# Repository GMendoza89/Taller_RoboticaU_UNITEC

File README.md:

# Taller_Robotica_UNITEC
Repositorio del taller de Robótica de la UNITEC Campus Queretaro. En el podras encontrar los ejemplos que que se van realizando durante el curso. 

## C++

Aqui encontraras los ejemplos que se realizaron en las clases de repaso de C++, y el paradigma orientado a objetos.

## Arduino

En esta seccion encontraras ejemplos de como construir tu propia libreria para generar las clases de tus componentes. Tambien encontraras los sketch, donde
se como declarar, y utilizar los sensores, actuadores y los diferentes módulos que puedan ser utilizados en Arduino.

### Hola_Mundo
Diferentes ejemplos de como crear el primer sketch de Arduino, el cual es prender y apagar un LED. 

### Analog_IO
Ejemplos de como declarar entradas y salidas analogicas.

### Digital_IO
Ejemplo de como utilizar entradas y salidas digitales.

### Libreria componentes
Libreria creada para el curso en que se tienen clases de componentes que se utilizan en los diferentes ejemplos. 
	- Clase LED. abtracción de un LED para su uso en IDE de Arduino.
	- Clase LED_RGB. Abstracción de LED RGB para su uso en IDE de Arduino.
	- Clase Buttom. Abstracción de un Switch o push buttom para su uso en IDE de Arduino.
	- Clase Pot. Abstracción de un potenciometro, para su uso en IDE de Arduino.
	- Clase shiftR74HC595. Abtracción para de circuito de desplazamiento para su uso en IDE de Arduino.
	- Clase ultrasonico. Abstracción de sensor ultrasonico HC-SR04. para su uso en IDE de Arduino.
	- Clase DC_Motor. Abtracción de un motor o motoreductor en CD, para su uso con un puente H y la IDE de Arduino.

## Robot Shield
Placa de circuito Impreso diseñada, como interface entre los sensores y actuadores de un robot diferencial, y una targeta de desarrollo Arduino UNO y compactibles.
Cuenta con las interfaces para los siguinetes puertos:
	- Coneccion con punte H L293D para control de dos motores en DC.
	- Un servomotor
	- Un Sensor Ultrasónico HC - SR04
	- Tira de sensores reflectivos compactibles con siguelineas
	- Modulo Bluetooth HC-06

## Python

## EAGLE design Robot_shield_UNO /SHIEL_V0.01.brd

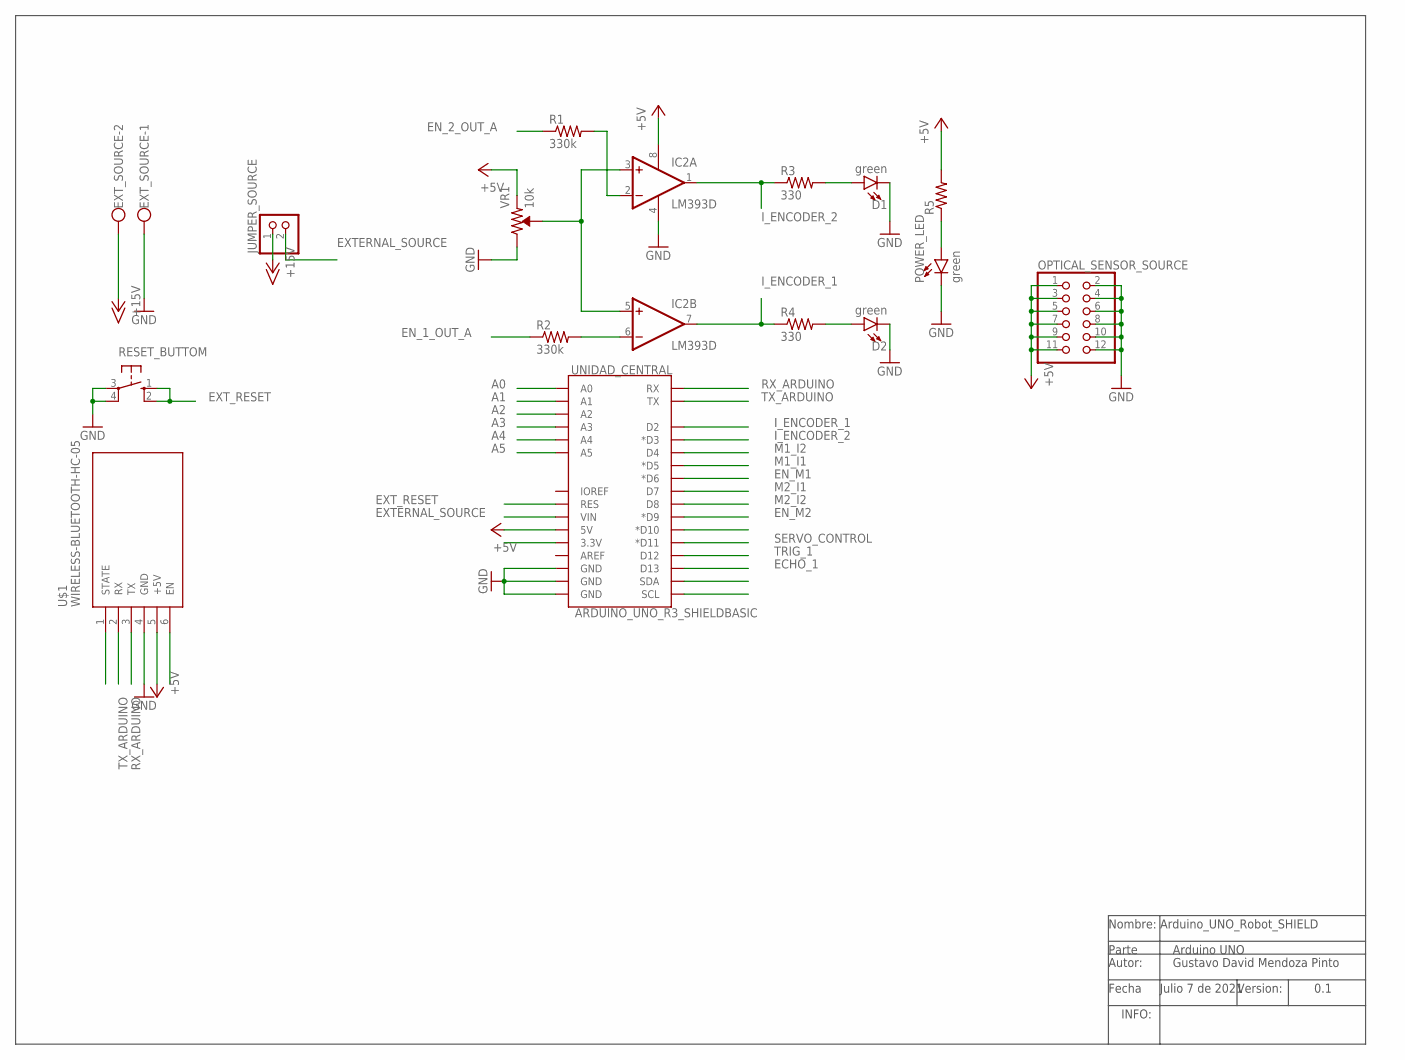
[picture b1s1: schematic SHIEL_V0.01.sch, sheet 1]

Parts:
D1, D2: green; LED_3MM-NS
EXT_SOURCE: W237-102
IC2: LM393D; SO08
JUMPER_SOURCE: PINHD-1X2; 1X02
OPTICAL_SENSOR_SOURCE: PINHD-2X6; 2X06
POWER_LED: green; LED_3MM-NS
R1, R2: 330k; M2012
R3, R4: 330; M2012
R5: R-US_M2012; M2012
RESET_BUTTOM: 10-XX; B3F-10XX
U$1: WIRELESS-BLUETOOTH-HC-05
UNIDAD_CENTRAL: ARDUINO_UNO_R3_SHIELDBASIC; UNO_R3_SHIELD
VR1: 10k; TRIMPOT-PTH-3386U

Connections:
+5V: IC2.8 (V+), OPTICAL_SENSOR_SOURCE.1, OPTICAL_SENSOR_SOURCE.3, OPTICAL_SENSOR_SOURCE.5, OPTICAL_SENSOR_SOURCE.7, OPTICAL_SENSOR_SOURCE.9, OPTICAL_SENSOR_SOURCE.11, R5.2, U$1.5 (+5V), UNIDAD_CENTRAL.5V, VR1.1 (CCW); also elsewhere on the board
+15V: EXT_SOURCE.2, JUMPER_SOURCE.1
A0: UNIDAD_CENTRAL.A0; also elsewhere on the board
A1: UNIDAD_CENTRAL.A1; also elsewhere on the board
A2: UNIDAD_CENTRAL.A2; also elsewhere on the board
A3: UNIDAD_CENTRAL.A3; also elsewhere on the board
A4: UNIDAD_CENTRAL.A4; also elsewhere on the board
A5: UNIDAD_CENTRAL.A5; also elsewhere on the board
ECHO_1: UNIDAD_CENTRAL.D13; also elsewhere on the board
EN_1_OUT_A: R2.1; also elsewhere on the board
EN_2_OUT_A: R1.1; also elsewhere on the board
EN_M1: UNIDAD_CENTRAL.D6 (*D6); also elsewhere on the board
EN_M2: UNIDAD_CENTRAL.D9 (*D9); also elsewhere on the board
EXTERNAL_SOURCE: JUMPER_SOURCE.2, UNIDAD_CENTRAL.VIN; also elsewhere on the board
EXT_RESET: RESET_BUTTOM.1 (S), RESET_BUTTOM.2 (S1), UNIDAD_CENTRAL.RES
GND: D1.K (C), D2.K (C), EXT_SOURCE.1, IC2.4 (V-), OPTICAL_SENSOR_SOURCE.2, OPTICAL_SENSOR_SOURCE.4, OPTICAL_SENSOR_SOURCE.6, OPTICAL_SENSOR_SOURCE.8, OPTICAL_SENSOR_SOURCE.10, OPTICAL_SENSOR_SOURCE.12, POWER_LED.K (C), RESET_BUTTOM.3, RESET_BUTTOM.4 (P1), U$1.4 (GND), UNIDAD_CENTRAL.GND@0 (GND), UNIDAD_CENTRAL.GND@1 (GND), UNIDAD_CENTRAL.GND@2 (GND), VR1.3 (CW); also elsewhere on the board
I_ENCODER_1: IC2.7 (OUT), R4.1, UNIDAD_CENTRAL.D2; also elsewhere on the board
I_ENCODER_2: IC2.1 (OUT), R3.1, UNIDAD_CENTRAL.D3 (*D3); also elsewhere on the board
M1_I1: UNIDAD_CENTRAL.D5 (*D5); also elsewhere on the board
M1_I2: UNIDAD_CENTRAL.D4; also elsewhere on the board
M2_I1: UNIDAD_CENTRAL.D7; also elsewhere on the board
M2_I2: UNIDAD_CENTRAL.D8; also elsewhere on the board
unnamed: IC2.3 (+IN), IC2.5 (+IN), VR1.2 (WIPER)
unnamed: IC2.2 (-IN), R1.2
unnamed: IC2.6 (-IN), R2.2
unnamed: POWER_LED.A, R5.1
unnamed: D1.A, R3.2
unnamed: D2.A, R4.2
RX_ARDUINO: U$1.3 (TX), UNIDAD_CENTRAL.RX
SERVO_CONTROL: UNIDAD_CENTRAL.D11 (*D11); also elsewhere on the board
TRIG_1: UNIDAD_CENTRAL.D12; also elsewhere on the board
TX_ARDUINO: U$1.2 (RX), UNIDAD_CENTRAL.TX

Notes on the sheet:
Nombre: Arduino_UNO_Robot_SHIELD
Autor:
Version:
Fecha
INFO:
Parte
Arduino UNO
Gustavo David Mendoza Pinto
Julio 7 de 2021
0.1

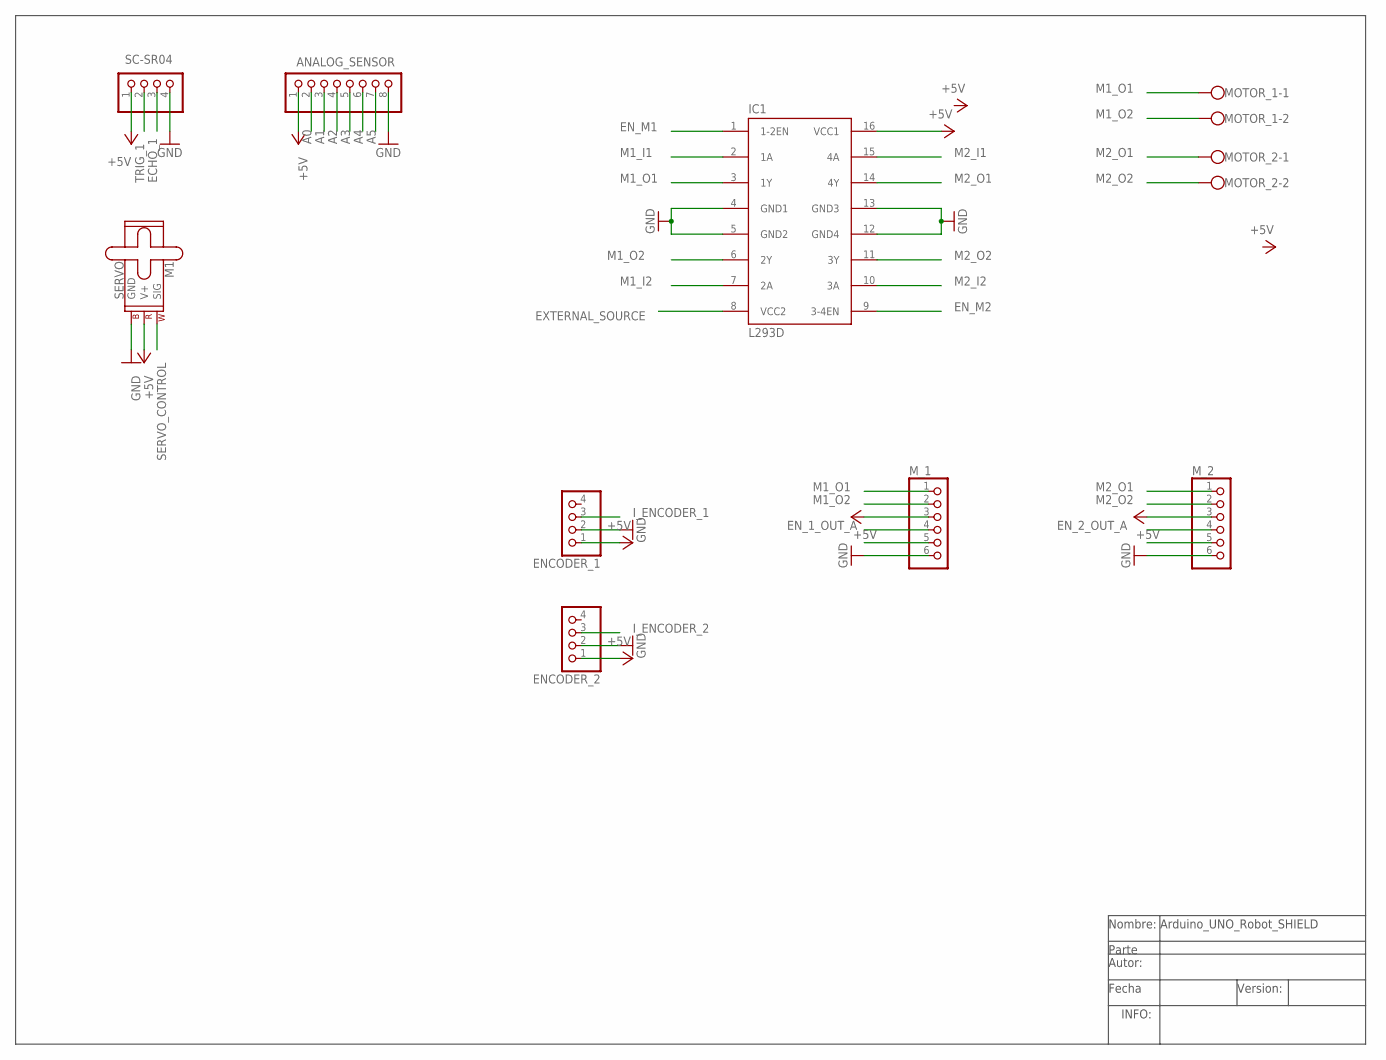
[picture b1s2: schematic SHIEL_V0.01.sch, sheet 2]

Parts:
ANALOG_SENSOR: PINHD-1X8; 1X08
ENCODER_1, ENCODER_2: PINHD-1X4; 1X04
IC1: L293D; DIL16
M1: SERVO; 1X03
MOTOR_1, MOTOR_2: W237-102
M_1, M_2: PINHD-1X6; 1X06
SC-SR04: PINHD-1X4; 1X04

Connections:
+5V: ANALOG_SENSOR.1, ENCODER_1.1, ENCODER_2.1, IC1.16 (VCC1), M1.2 (V+), M_1.3, M_2.3, SC-SR04.1; also elsewhere on the board
A0: ANALOG_SENSOR.2; also elsewhere on the board
A1: ANALOG_SENSOR.3; also elsewhere on the board
A2: ANALOG_SENSOR.4; also elsewhere on the board
A3: ANALOG_SENSOR.5; also elsewhere on the board
A4: ANALOG_SENSOR.6; also elsewhere on the board
A5: ANALOG_SENSOR.7; also elsewhere on the board
ECHO_1: SC-SR04.3; also elsewhere on the board
EN_1_OUT_A: M_1.4; also elsewhere on the board
EN_2_OUT_A: M_2.4; also elsewhere on the board
EN_M1: IC1.1 (1-2EN); also elsewhere on the board
EN_M2: IC1.9 (3-4EN); also elsewhere on the board
EXTERNAL_SOURCE: IC1.8 (VCC2); also elsewhere on the board
GND: ANALOG_SENSOR.8, ENCODER_1.2, ENCODER_2.2, IC1.4 (GND1), IC1.5 (GND2), IC1.12 (GND4), IC1.13 (GND3), M1.3 (GND), M_1.6, M_2.6, SC-SR04.4; also elsewhere on the board
I_ENCODER_1: ENCODER_1.3; also elsewhere on the board
I_ENCODER_2: ENCODER_2.3; also elsewhere on the board
M1_I1: IC1.2 (1A); also elsewhere on the board
M1_I2: IC1.7 (2A); also elsewhere on the board
M1_O1: IC1.3 (1Y), MOTOR_1.1, M_1.1
M1_O2: IC1.6 (2Y), MOTOR_1.2, M_1.2
M2_I1: IC1.15 (4A); also elsewhere on the board
M2_I2: IC1.10 (3A); also elsewhere on the board
M2_O1: IC1.14 (4Y), MOTOR_2.1, M_2.1
M2_O2: IC1.11 (3Y), MOTOR_2.2, M_2.2
SERVO_CONTROL: M1.1 (SIG); also elsewhere on the board
TRIG_1: SC-SR04.2; also elsewhere on the board

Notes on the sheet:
Nombre: Arduino_UNO_Robot_SHIELD
Autor:
Version:
Fecha
INFO:
Parte

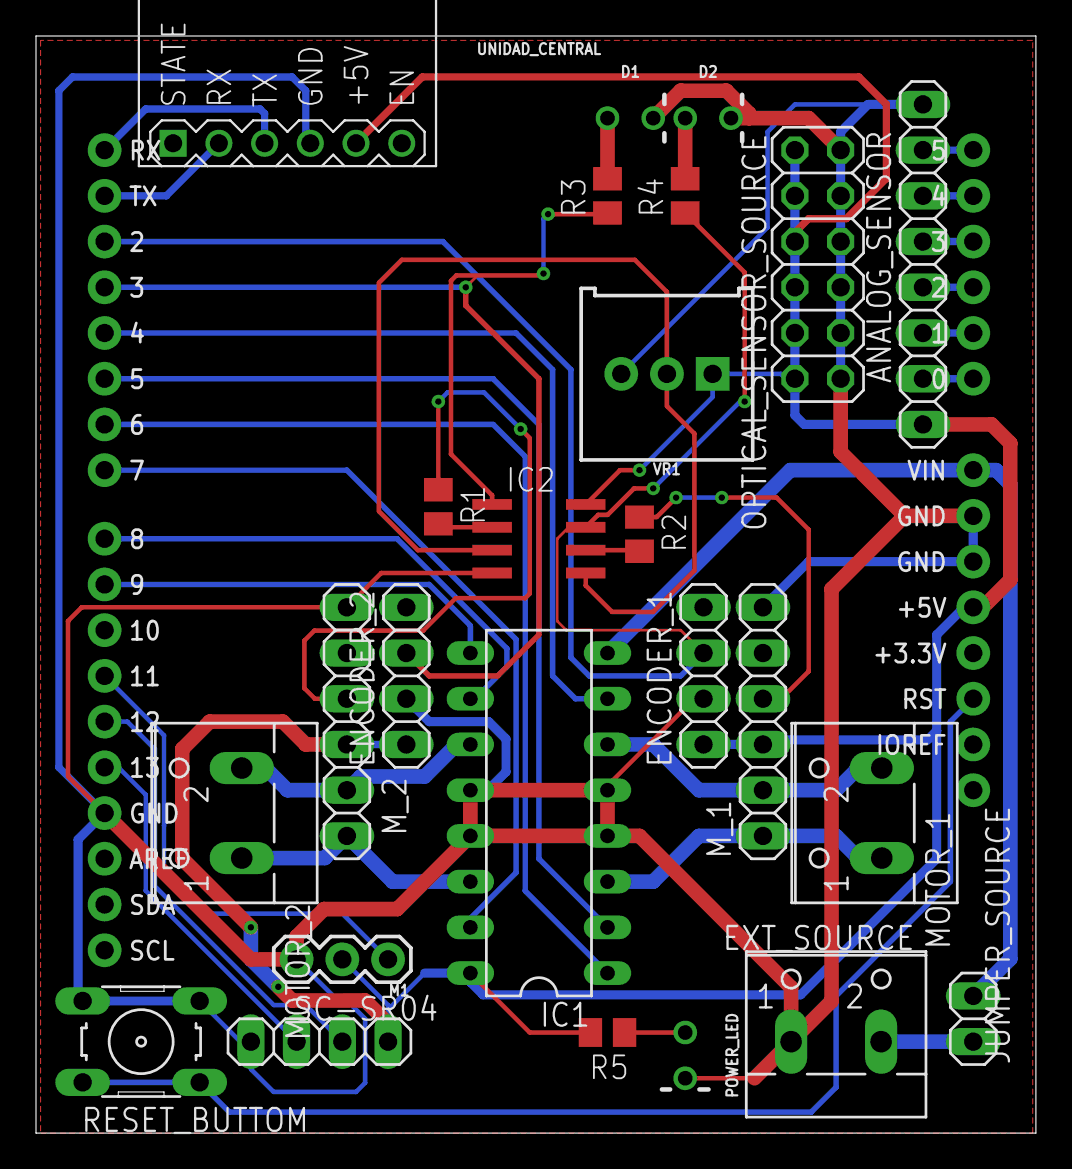
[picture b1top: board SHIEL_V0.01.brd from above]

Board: 2 copper layers, 55.5 x 61.0 mm, 26 parts (0 on the bottom side), 36 nets.

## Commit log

2021-02-19 Hola Mundo en c++ visto en el taller el dia 18 de noviembre de 2021
2021-02-24 Se agregan los codigos vistos en la sesion del dia 23 de febrero de 2021
2021-02-24 Se agrega memoria dinamica, y se genera archivo de salida
2021-02-24 Se apuede variar la cantidad de argumentos dee 2 a cuatro en el programa, argumento 2 la cantidad de elementos en la serie, argumento 3 el nombre de fichero de salida, argumento 4 la extencion para e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
2021-02-25 Ejemplo de matrices clase del dia jueves 25 de febrero
2021-02-25 Se incorporan funciones a la libreria de matrices
2021-02-25 Ejemplo de clase
2021-03-02 Ejemplos de lectura y salidas digitales con arduino. Ejemplo de libreria en arduino con clases definidas para led y boton
2021-03-05 Se incorporan clases de led rgb y potenciometro, ejemplo de lectura y salida analogica
2021-03-10 Se incorporan clases y programa de registro de desplazamiento visto en clase
2021-03-10 Se incorpora ejemplo de hola Mundo con Libreria
2021-03-16 Se incorporan ejemplos de lecturas de sensores reflectivos y de sensores de proximidad
2021-03-25 Aplicacion de control Bluetooth desarrollada en appinventor2
2021-03-25 Se agregan ejemplo para carro controlado con Bluetooth
2021-03-25 Se agrega descripcion del Repositorio
2021-04-05 Aplicacion de android desarrollada durante el el taller para importarla en appInventor2 (https://appinventor.mit.edu/).
2021-04-05 Actualización de programas creados en durante el repaso de c++
2021-07-14 Se incorpora Shield para Arduino UNO
2021-07-14 Captura de patalla de tarjeta de la Shield
2021-07-14 Descripción rápida de shield
2021-07-14 Se inicializa la implementación de la libreria para IDE de ARDUINO
2021-07-16 Se incorpora la clase del sensor ultrasonico
2021-07-16 Se incorporan las funciones de la clase ultrasonico, y se usa ejemplo de libreria Servo.h
2021-07-23 Se incorppora implementacion de odometria con robot wall-e
2023-03-03 Se incorpora libreria de de componentes de robots en version 0.1.0
2023-03-03 Se incorpora ejemplo control de robot Sumo

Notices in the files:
parts and their libraries:
SparkFun-Boards: Licensing: Creative Commons ShareAlike 4.0 International - https://creativecommons.org/licenses/by-sa/4.0
diy-modules: Released under the Creative Commons Attribution 4.0 International License: http://creativecommons.org/licenses/by/4.0
